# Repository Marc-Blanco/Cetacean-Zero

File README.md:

# 🐋 Cetacean Zero

A compact, open-source multi-tool handheld device inspired by the Flipper Zero, built around the **STMicroelectronics NUCLEO-F411RE** development board. It packs wireless communication, GNSS, NFC, IR transceiving, and a game-controller-style input layout into a single portable PCB.

---

## Overview

| Capability | Hardware | Interface |
|---|---|---|
| Sub-GHz RF transmit | Si4012-C1001xT | I²C (SPI-like via SCL/SDA) |
| NFC (contactless) | PN5321A3HN | I²C/SPI |
| GNSS positioning | u-blox MAX-M10S | UART |
| IR transmit/receive | Si4012 TX + TSOP38238 RX | GPIO / Timer PWM |
| Display | 2.8″ HS280S010B TFT (240×320) | SPI |
| Storage | MicroSD card slot | SPI |
| Power | USB-C input + TP4056 LiPo charger | — |
| Input | 8-button game controller layout | GPIO |
| Audio | Passive speaker/buzzer | GPIO (driver TBD) |

---

## Hardware Architecture

### Compute — NUCLEO64-F411RE
The STM32F411RE sits at the heart of the system. It runs at up to 100 MHz with an FPU (Cortex-M4), has 512 KB Flash and 128 KB RAM, and connects to all peripherals via its two 2×32 morpho connectors. The Nucleo's onboard ST-Link provides USB programming and UART debug out of the box.

### Power
USB-C (5 V) charges a single-cell LiPo battery via a **TP4056** linear charger IC. The CC1/CC2 pull-down resistors (5.1 kΩ each) are present for correct USB-C sink detection. Four 22 Ω series resistors cover the USB D+/D− pads for signal integrity.

> ⚠ **A 3.3 V LDO regulator and LiPo protection circuit are required** but not yet placed in the schematic. See the schematic review for details.

### Wireless
- **Sub-GHz RF (Si4012):** Transmits in the sub-GHz ISM bands. Frequency is set by an external 30 MHz crystal reference (not yet placed). Useful for replaying garage doors, remote controls, and other OOK/ASK signals.
- **NFC (PN5321A3HN):** Supports ISO 14443 / ISO 18092 for reading and emulating NFC-A/B/F cards and tags. Requires an external PCB coil antenna and matching circuit (not yet placed).
- **IR (TSOP38238 + Si4012):** 38 kHz IR receiver decodes remote control signals. IR transmission is handled via the Si4012's output stage driving an IR LED.

### GNSS
The **u-blox MAX-M10S** provides GPS/GNSS positioning. It communicates over UART to the STM32.

### Display & Storage
A 2.8″ 240×320 TFT (**HS280S010B**) connects over SPI for the main UI. A MicroSD card slot shares the SPI bus for firmware assets, signal capture logs, and config storage.

### Input
Eight tactile push buttons provide a Flipper-style navigation layout: D-pad (Up/Down/Left/Right), Back, and two shoulder buttons. A DPDT slide switch handles power on/off.

---

## Bill of Materials

See [`cetacean_zero_bom.csv`](./cetacean_zero_bom.csv) for the full component list with recommended footprints, LCSC part numbers where available, and per-component notes on outstanding issues.

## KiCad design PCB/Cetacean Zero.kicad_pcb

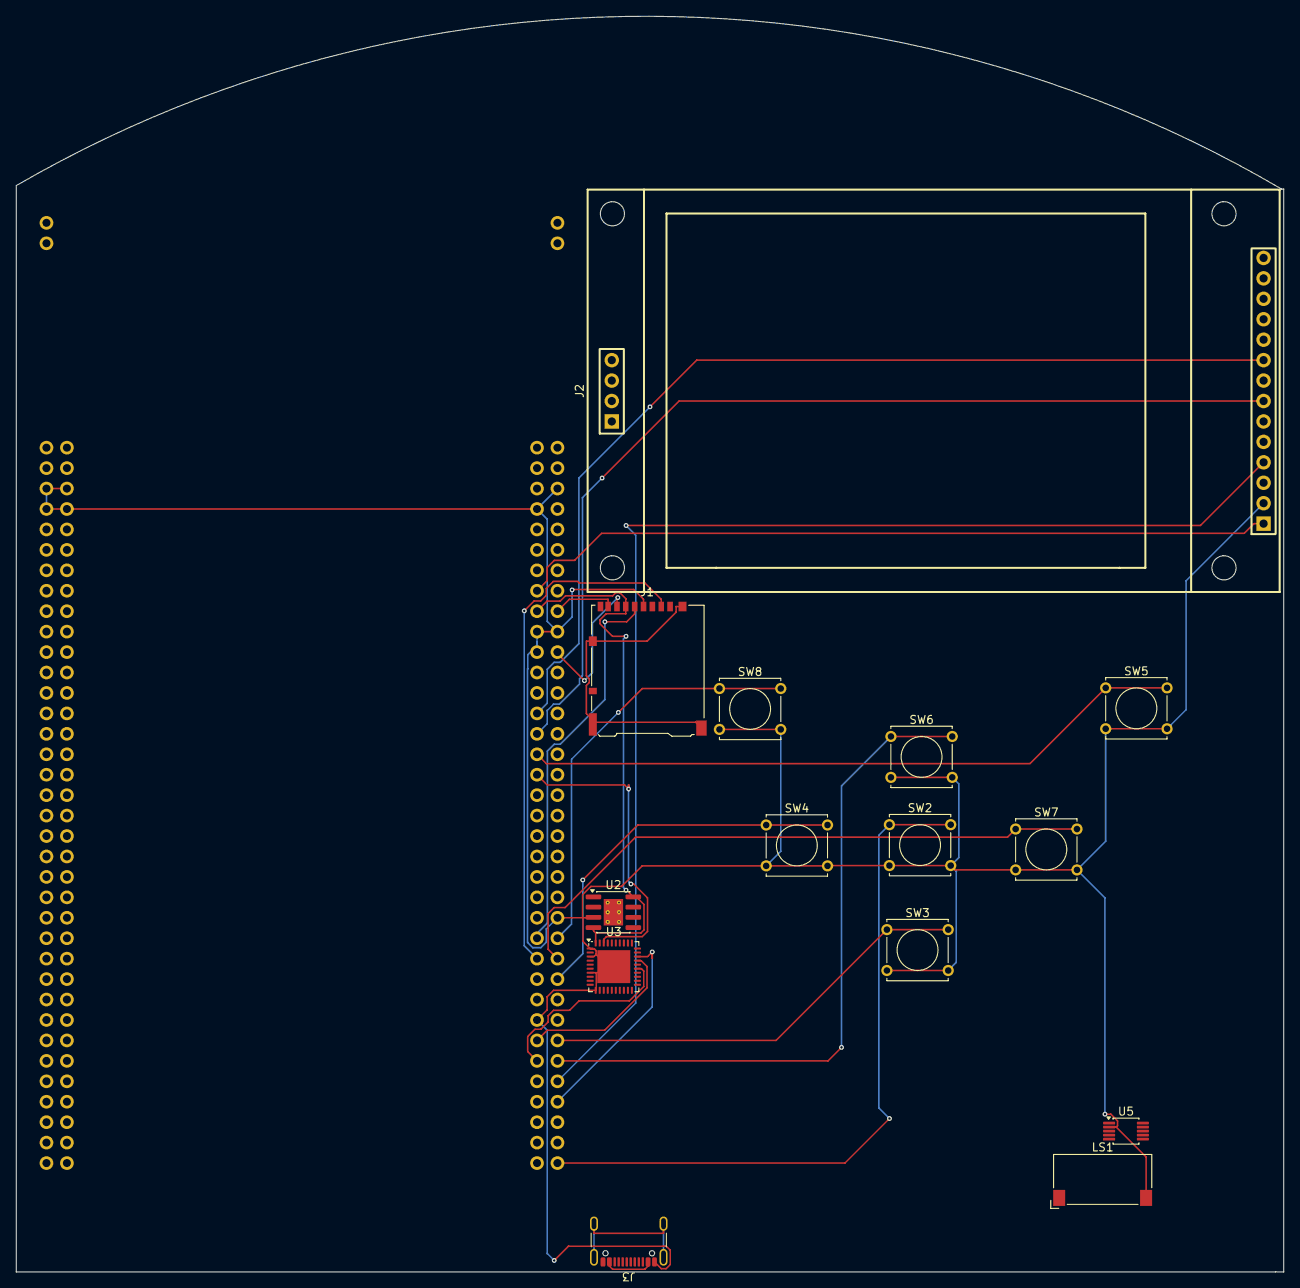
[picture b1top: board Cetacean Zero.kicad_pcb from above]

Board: 2 copper layers, 157.5 x 156.0 mm, 15 parts (1 on the bottom side), 21 nets.

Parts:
J1: Micro_SD_Card; microSD_HC_Hirose_DM3AT-SF-PEJM5
J2: LCD-TH_HS280S010B
J3: USB_C_Receptacle; USB_C_Receptacle_GCT_USB4105-xx-A_16P_TopMnt_Horizontal
LS1: Speaker; Speaker_CUI_CMR-1206S-67
SW2: Back; SW_Tactile_Straight_KSA0Axx1LFTR
SW3: Down; SW_Tactile_Straight_KSA0Axx1LFTR
SW4: Left; SW_Tactile_Straight_KSA0Axx1LFTR
SW5: Shoulder2; SW_Tactile_Straight_KSA0Axx1LFTR
SW6: Up; SW_Tactile_Straight_KSA0Axx1LFTR
SW7: Right; SW_Tactile_Straight_KSA0Axx1LFTR
SW8: Shoulder; SW_Tactile_Straight_KSA0Axx1LFTR
U1: NUCLEO64-F411RE; ST_Morpho_Connector_144_STLink
U2: TP4056-42-ESOP8; SOIC-8-1EP_3.9x4.9mm_P1.27mm_EP2.41x3.3mm_ThermalVias
U3: PN5321A3HN_C1xx; HVQFN-40-1EP_6x6mm_P0.5mm_EP4.1x4.1mm
U5: Si4012-C1001xT; MSOP-10_3x3mm_P0.5mm

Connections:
+3.3V: J2.1 (VCC), U1.16 (+3V3)
+5V: J1.6 (VSS), J3.A4 (VBUS), J3.A9 (VBUS), J3.B4 (VBUS), J3.B9 (VBUS), U1.18 (+5V), U2.4 (V_{CC}), U2.8 (CE), U3.40 (VBAT)
Back: SW2.1, U1.71 (PA10)
Down: SW3.1, U1.59 (PA9)
GND: J1.4 (VDD), J2.2 (GND), J3.A1 (GND), J3.A12 (GND), J3.B1 (GND), J3.B12 (GND), LS1.2, SW2.2, SW3.2, SW4.2, SW5.2, SW6.2, SW7.2, SW8.2, U1.5 (VDD), U1.8 (GND), U1.19 (GND), U1.20 (GND), U1.22 (GND), U1.47 (GND), U1.58 (GND), U1.77 (GND), U1.78 (GND), U1.79 (GND), U1.80 (GND), U2.3 (GND), U3.1 (DVSS), U3.3 (TVSS1), U3.7 (TVSS2), U3.11 (AVSS), U3.41 (AVSS), U5.2 (GND_2)
J2_CS: J1.2 (DAT3/CD), U1.52 (PA11)
J2_MISO: J1.7 (DAT0), U1.21 (PB7)
J2_MOSI: J1.8 (DAT1), U1.17 (PA15)
J2_SCK: J1.5 (CLK), U1.50 (PA12)
Left: SW4.1, U1.53 (PA7)
RST: J2.4 (RST), U1.63 (PB10)
Right: SW7.1, U1.51 (PA6)
SCL: J2.7 (SCL), U1.30 (PA1)
SDA: J2.9 (SDO), U1.28 (PA0)
Sh1: SW8.1, U1.49 (PA5)
Sh2: SW5.1, U1.32 (PA4)
U3_IRQ: U1.62 (PB1), U3.25 (P70_IRQ)
U3_RST: U1.34 (PB0), U3.38 (~RSTPD)
U3_SCL: U1.60 (PB2), U3.27 (NSS/P50_SCL/HSU_RX)
U3_SDA: U1.65 (PB4), U3.28 (MOSI/SDA/HSU_TX)
Up: SW6.1, U1.61 (PA8)
